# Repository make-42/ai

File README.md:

# ai

[Youtube video documenting the design process](https://youtu.be/T9ol78Huxd8)

This is a small open source 5x4-1 macropad powered by QMK

* Keyboard Maintainer: [Louis Dalibard](https://github.com/make42)
* Hardware Supported: The PCB for ai is located here: [ai](https://github.com/make42/ai)
* Hardware Availability: Here is a complete BOM with links to where you can find parts:
  * PCB (I personally used JLCPCB)
  * Arduino Pro Micro ([Aliexpress](https://fr.aliexpress.com/item/32768308647.html?spm=a2g0o.order_list.0.0.3ccc5e5bU64POK&gatewayAdapt=glo2fra))
  * Female pin rows ([Aliexpress](https://fr.aliexpress.com/item/4001122376295.html?spm=a2g0o.order_list.0.0.23845e5bTBt8sp&gatewayAdapt=glo2fra))
  * Gateron hotswap sockets ([Aliexpress](https://fr.aliexpress.com/item/1005003129613578.html?spm=a2g0o.order_list.0.0.23845e5bTBt8sp&gatewayAdapt=glo2fra))
  * Zener diodes ([Aliexpress](https://fr.aliexpress.com/item/1005003276184193.html?spm=a2g0o.order_list.0.0.23845e5bTBt8sp&gatewayAdapt=glo2fra))
  * Keyswitches (use a compatible MX switch)
  * Keycaps (Duh)

Make example for this keyboard (after setting up your build environment):

    make ai:default

Flashing example for this keyboard:

    make ai:default:flash

See the [build environment setup](https://docs.qmk.fm/#/getting_started_build_tools) and the [make instructions](https://docs.qmk.fm/#/getting_started_make_guide) for more information. Brand new to QMK? Start with our [Complete Newbs Guide](https://docs.qmk.fm/#/newbs).

## Bootloader

Enter the bootloader in 3 ways:

-   **Bootmagic reset**: Hold down the key at (0,0) in the matrix (usually the top left key or Escape) and plug in the keyboard
-   **Physical reset button**: Briefly press the button on the back of the PCB - some may have pads you must short instead
-   **Keycode in layout**: Press the key mapped to `RESET` if it is available

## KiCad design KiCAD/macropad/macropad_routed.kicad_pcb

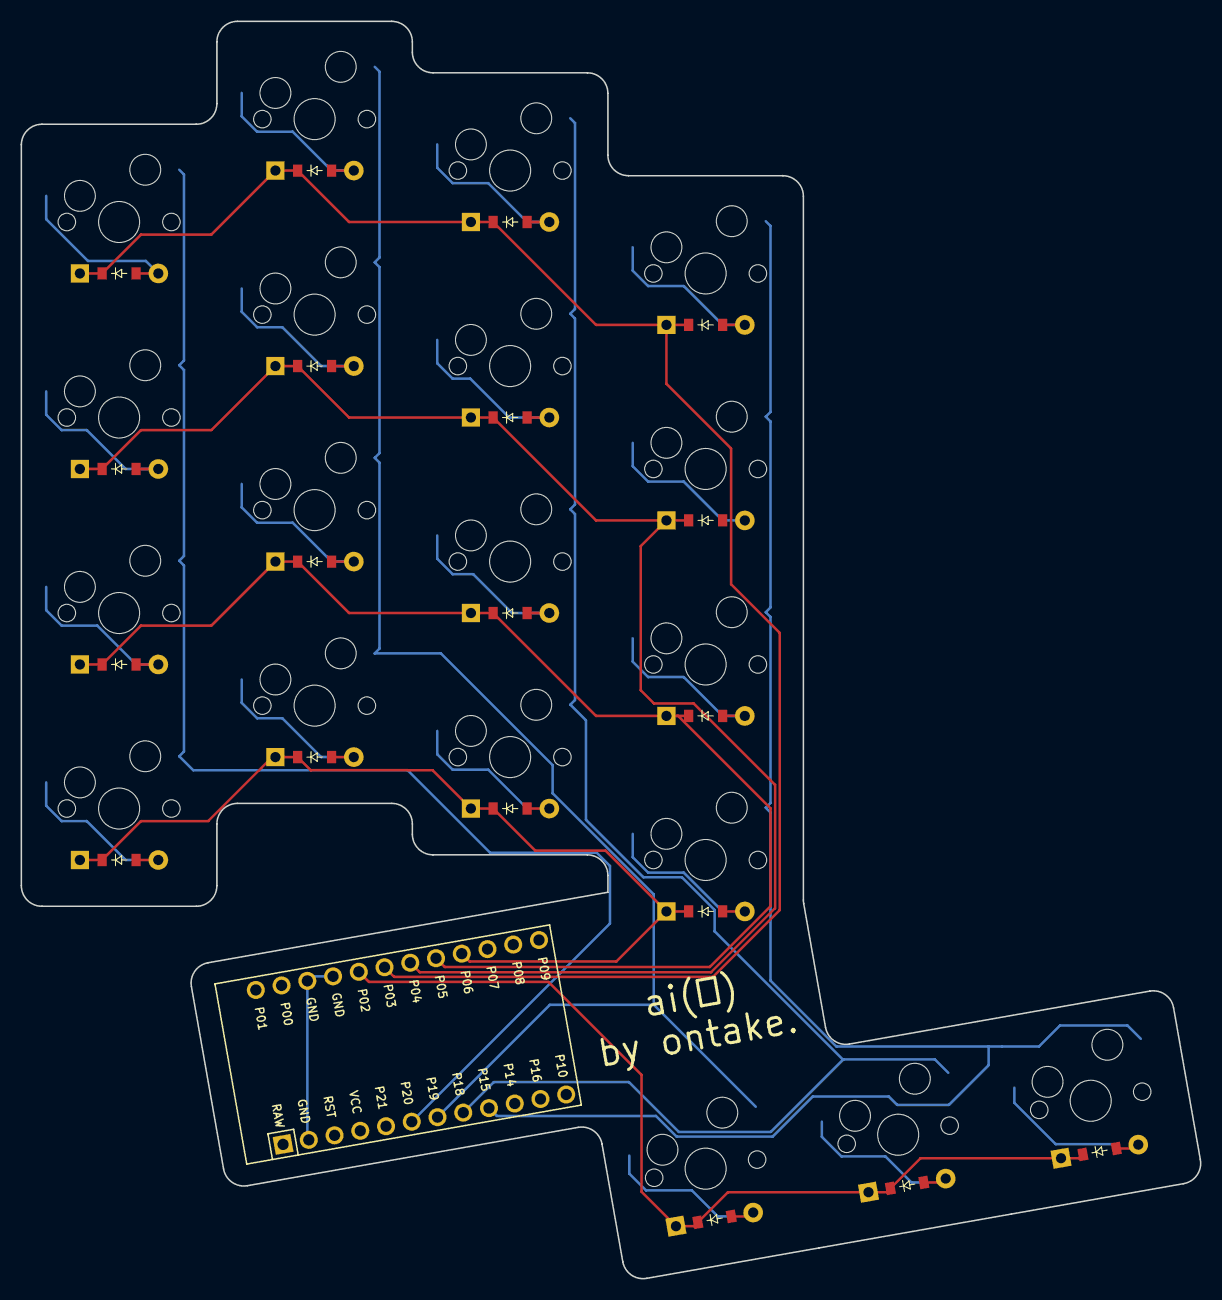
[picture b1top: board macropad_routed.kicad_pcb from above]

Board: 2 copper layers, 114.6 x 122.2 mm, 39 parts (0 on the bottom side), 29 nets.

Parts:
D1, D2, D3, D4, D5, D6, D7, D8, D9, D10, D11, D12, D13, D14, D15, D16, D17, D18, D19: ComboDiode
MCU1: ProMicro
S1, S2, S3, S4, S5, S6, S7, S8, S9, S10, S11, S12, S13, S14, S15, S16, S17, S18, S19: MX

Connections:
GND: MCU1.2, MCU1.15, MCU1.16
P2: D17.1, D17.2, D18.1, D18.2, D19.1, D19.2, MCU1.17
P3: D4.1, D4.2, D8.1, D8.2, D12.1, D12.2, D16.1, D16.2, MCU1.18
P4: D3.1, D3.2, D7.1, D7.2, D11.1, D11.2, D15.1, D15.2, MCU1.19
P5: D2.1, D2.2, D6.1, D6.2, D10.1, D10.2, D14.1, D14.2, MCU1.20
P6: D1.1, D1.2, D5.1, D5.2, D9.1, D9.2, D13.1, D13.2, MCU1.21
P15: MCU1.9, S13.2, S14.2, S15.2, S16.2, S19.2
P18: MCU1.8, S9.2, S10.2, S11.2, S12.2, S18.2
P19: MCU1.7, S5.2, S6.2, S7.2, S8.2, S17.2
P20: MCU1.6, S1.2, S2.2, S3.2, S4.2
c1_r1: D1.1, D1.2, S1.1
c1_r2: D2.1, D2.2, S2.1
c1_r3: D3.1, D3.2, S3.1
c1_r4: D4.1, D4.2, S4.1
c2_r1: D5.1, D5.2, S5.1
c2_r2: D6.1, D6.2, S6.1
c2_r3: D7.1, D7.2, S7.1
c2_r4: D8.1, D8.2, S8.1
c3_r1: D9.1, D9.2, S9.1
c3_r2: D10.1, D10.2, S10.1
c3_r3: D11.1, D11.2, S11.1
c3_r4: D12.1, D12.2, S12.1
c4_r1: D13.1, D13.2, S13.1
c4_r2: D14.1, D14.2, S14.1
c4_r3: D15.1, D15.2, S15.1
c4_r4: D16.1, D16.2, S16.1
c5_r5: D17.1, D17.2, S17.1
c6_r5: D18.1, D18.2, S18.1
c7_r5: D19.1, D19.2, S19.1

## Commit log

2022-07-19 Add some documentation
2022-07-19 Add Ai keyboard
2022-07-19 Add basic blender file
2022-07-19 add v2 blender file
2022-07-20 Fix probleme with rounding of the tracks
2022-07-20 Sync changes to firmware
2022-07-21 fix documentation
2024-05-08 feat: add laser cutting files
